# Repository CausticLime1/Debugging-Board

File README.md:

# sharkbyte

STM32H723 firmware for the SharkByte board.

## Prerequisites

- **Windows** (the build toolchain runs via PowerShell)
- **VSCode** with the [STM32 VSCode Extension](https://marketplace.visualstudio.com/items?itemName=stmicroelectronics.stm32-vscode-extension) installed
- **STM32CubeMX** 6.15.0+

## Getting started

### 1. Clone

```bash
git clone --recurse-submodules <repo-url>
```

### 2. Regenerate CubeMX files

Most of the ST-generated HAL and middleware files are not checked in — they're derived from `sharkbyte.ioc`. Regenerate them with:

**Command Palette → Run Task → STM32: CubeMX Codegen**

Or from the terminal:
```powershell
powershell -File .vscode/stm32cube.ps1 codegen
```

### 3. Build

**Command Palette → Run Task → STM32: Build Debug**

Or:
```powershell
powershell -File .vscode/stm32cube.ps1 build
```

### 4. Flash

Connect an ST-Link and run:

**Command Palette → Run Task → STM32: Flash And Run Debug**

This builds, flashes, and resets the board.

## Project structure

```
sharkbyte.ioc       # CubeMX project — source of truth for chip config
CMakeLists.txt      # Top-level build (manually maintained)
Core/Src/main.c     # Application entry point
Core/Src/encoder.cpp
Core/Inc/
gui/                # LVGL UI code
.vscode/
  stm32cube.ps1     # Build/flash/codegen script
  tasks.json        # VSCode task definitions
```

## Notes

- `Drivers/`, `Middlewares/` are gitignored — they are regenerated by CubeMX and should not be edited by hand
- The ST bundle versions (compiler, CMake, etc.) are pinned in `.settings/bundles-lock.store.json` and downloaded automatically by the ST extension on first open
- USB init function is disabled in CubeMX

### Linker script

The build uses `STM32H723XG_FLASH_custom.ld` (not the CubeMX-generated `STM32H723XG_FLASH.ld`). The custom file differs in three ways:

- `FLASH` region trimmed from 1024 KB to 896 KB (sectors 0–6)
- `NV_STORAGE` region added at sector 7 (`0x080E0000`, 128 KB) for persistent settings
- `.dma_buf` section placed at a fixed address in RAM_D1 (`0x24010000`, after the 64 KB LVGL heap) — LVGL draw buffers must live in the CPU's D1 domain to avoid the STM32H7 D1→D2 interconnect write-buffer coherency issue with DMA1

CubeMX regeneration overwrites `STM32H723XG_FLASH.ld` but does not touch the custom file. If the device config changes in a way that affects flash or RAM layout (e.g. stack/heap sizes), diff `STM32H723XG_FLASH.ld` against `STM32H723XG_FLASH_custom.ld` and merge any relevant changes manually.

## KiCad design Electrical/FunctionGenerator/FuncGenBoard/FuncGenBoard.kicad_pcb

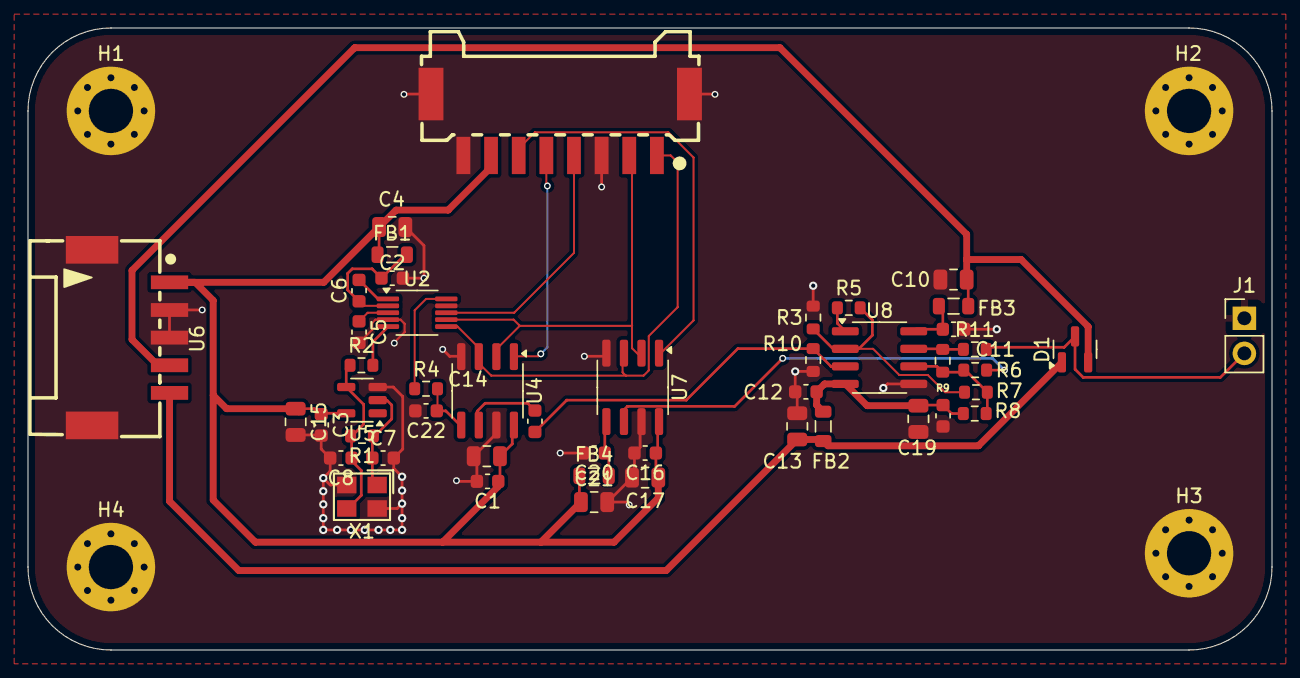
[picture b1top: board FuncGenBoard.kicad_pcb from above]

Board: 2 copper layers, 90.0 x 45.0 mm, 51 parts (0 on the bottom side), 28 nets.

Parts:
C1, C2, C3, C5, C11, C12, C16, C18, C20: 100nF; C_0603_1608Metric
C4, C9, C10, C13, C15, C17, C19, C21: 10uF; C_0805_2012Metric
C6: 10nF; C_0603_1608Metric
C7, C8: 18pF; C_0603_1608Metric
C14: 1uF; C_0603_1608Metric
C22: 100p; C_0603_1608Metric
D1: BAT54S; SOT-23
FB1, FB2, FB3, FB4: 600R@100MHz; L_0805_2012Metric
H1, H2, H3, H4: MountingHole_Pad; MountingHole_3.2mm_M3_Pad_Via
J1: Conn_01x02_Pin; PinHeader_1x02_P2.54mm_Vertical
R1: 1M; R_0603_1608Metric
R2: 33; R_0603_1608Metric
R3: 1k; R_0603_1608Metric
R4: 220; R_0603_1608Metric
R5: 4k; R_0603_1608Metric
R6, R7: 5.6k; R_0603_1608Metric
R8: 39K; R_0603_1608Metric
R9: 39k; R_0603_1608Metric
R10: 100k; R_0603_1608Metric
R11: 50; R_0603_1608Metric
U2: AD9833xRM; MSOP-10_3x3mm_P0.5mm
U4, U7: MCP4151-xxxx-P; SOIC-8_3.9x4.9mm_P1.27mm
U5: SN74LVC1GU04DBVR; SOT-23-5
U6: SM05B-PASS-TBT(LF)(SN); CONN-SMD_5P-P2.00_SM05B-PASS-TBT-LF-SN
U8: LM6172IMX/NOPB; SOIC-8_3.9x4.9mm_P1.27mm
U14: SM08B-PASS-TBT(LF)(SN); CONN-SMD_SM08B-PASS-TBT-LF-SN
X1: X322525MOB4SI; CRYSTAL-SMD_4P-L3.2-W2.5-BL

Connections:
+3.3V: C1.1, C3.1, C4.1, C9.1, C15.1, C16.1, C17.1, C21.1, FB1.1, FB4.1, U4.8 (V_{DD}), U5.5 (VCC), U6.1, U7.8 (V_{DD}), U14.7
+12V: C10.1, D1.2 (K), FB3.2, U6.4
-12V: C13.1, D1.1 (A), FB2.1, U6.5
/3.3_DIGI: C20.1, FB4.2, U7.5 (P0A)
/A_NINV: C14.1, R10.1, U8.3 (INA+)
/A_OUT: R3.1, R5.2, R7.1, U8.2 (INA-)
/B_OUT: R9.2, R11.1, U8.7 (OUTB)
/CS_AD9833: U2.8 (~FSYNC), U14.4
/CS_GAIN: U4.1 (~CS), U14.5
/CS_OFFSET: U7.1 (~CS), U14.6
/DIGI_OFST: R6.2, U7.6 (P0W)
/GEN_OUT: C22.1, R4.2, U4.5 (P0A)
/MCLK: R2.2, U2.5 (MCLK)
/SCLK: U2.7 (SCLK), U4.2 (SCK), U7.2 (SCK), U14.2
/SDATA: U2.6 (SDATA), U4.3 (SDI/SDO), U7.3 (SDI/SDO), U14.1
/V+: C11.1, FB3.1, U8.8 (V+)
/V-: C12.1, C18.1, C19.1, FB2.2, R8.1, U8.4 (V-)
GND: C1.2, C2.2, C3.2, C4.2, C5.2, C7.2, C8.2, C9.2, C10.2, C11.2, C12.2, C13.2, C15.2, C16.2, C17.2, C18.2, C19.2, C20.2, C21.2, C22.2, H1.1, H2.1, H3.1, H4.1, J1.1, R3.2, R10.2, U2.4 (DGND), U2.9 (AGND), U4.4 (V_{SS}), U4.7 (P0B), U5.3 (GND), U6.2, U6.3, U6.6, U6.7, U7.4 (V_{SS}), U7.7 (P0B), U8.5 (INB+), U14.3, U14.8, U14.9, U14.10, X1.2 (GND), X1.4 (GND)
unnamed: D1.3 (COM), J1.2, R11.2
unnamed: C5.1, U2.3 (CAP/2.5V)
unnamed: C6.2, U2.1 (COMP)
unnamed: C2.1, C6.1, FB1.2, U2.2 (VDD)
unnamed: R4.1, U2.10 (VOUT)
unnamed: C14.2, U4.6 (P0W)
unnamed: C7.1, R1.1, U5.2 (A), X1.1 (OSC1)
unnamed: C8.1, R1.2, R2.1, U5.4 (Y), X1.3 (OSC2)
unnamed: R6.1, R7.2, R8.2, R9.1, U8.6 (INB-)
unnamed: R5.1, U8.1 (OUTA)

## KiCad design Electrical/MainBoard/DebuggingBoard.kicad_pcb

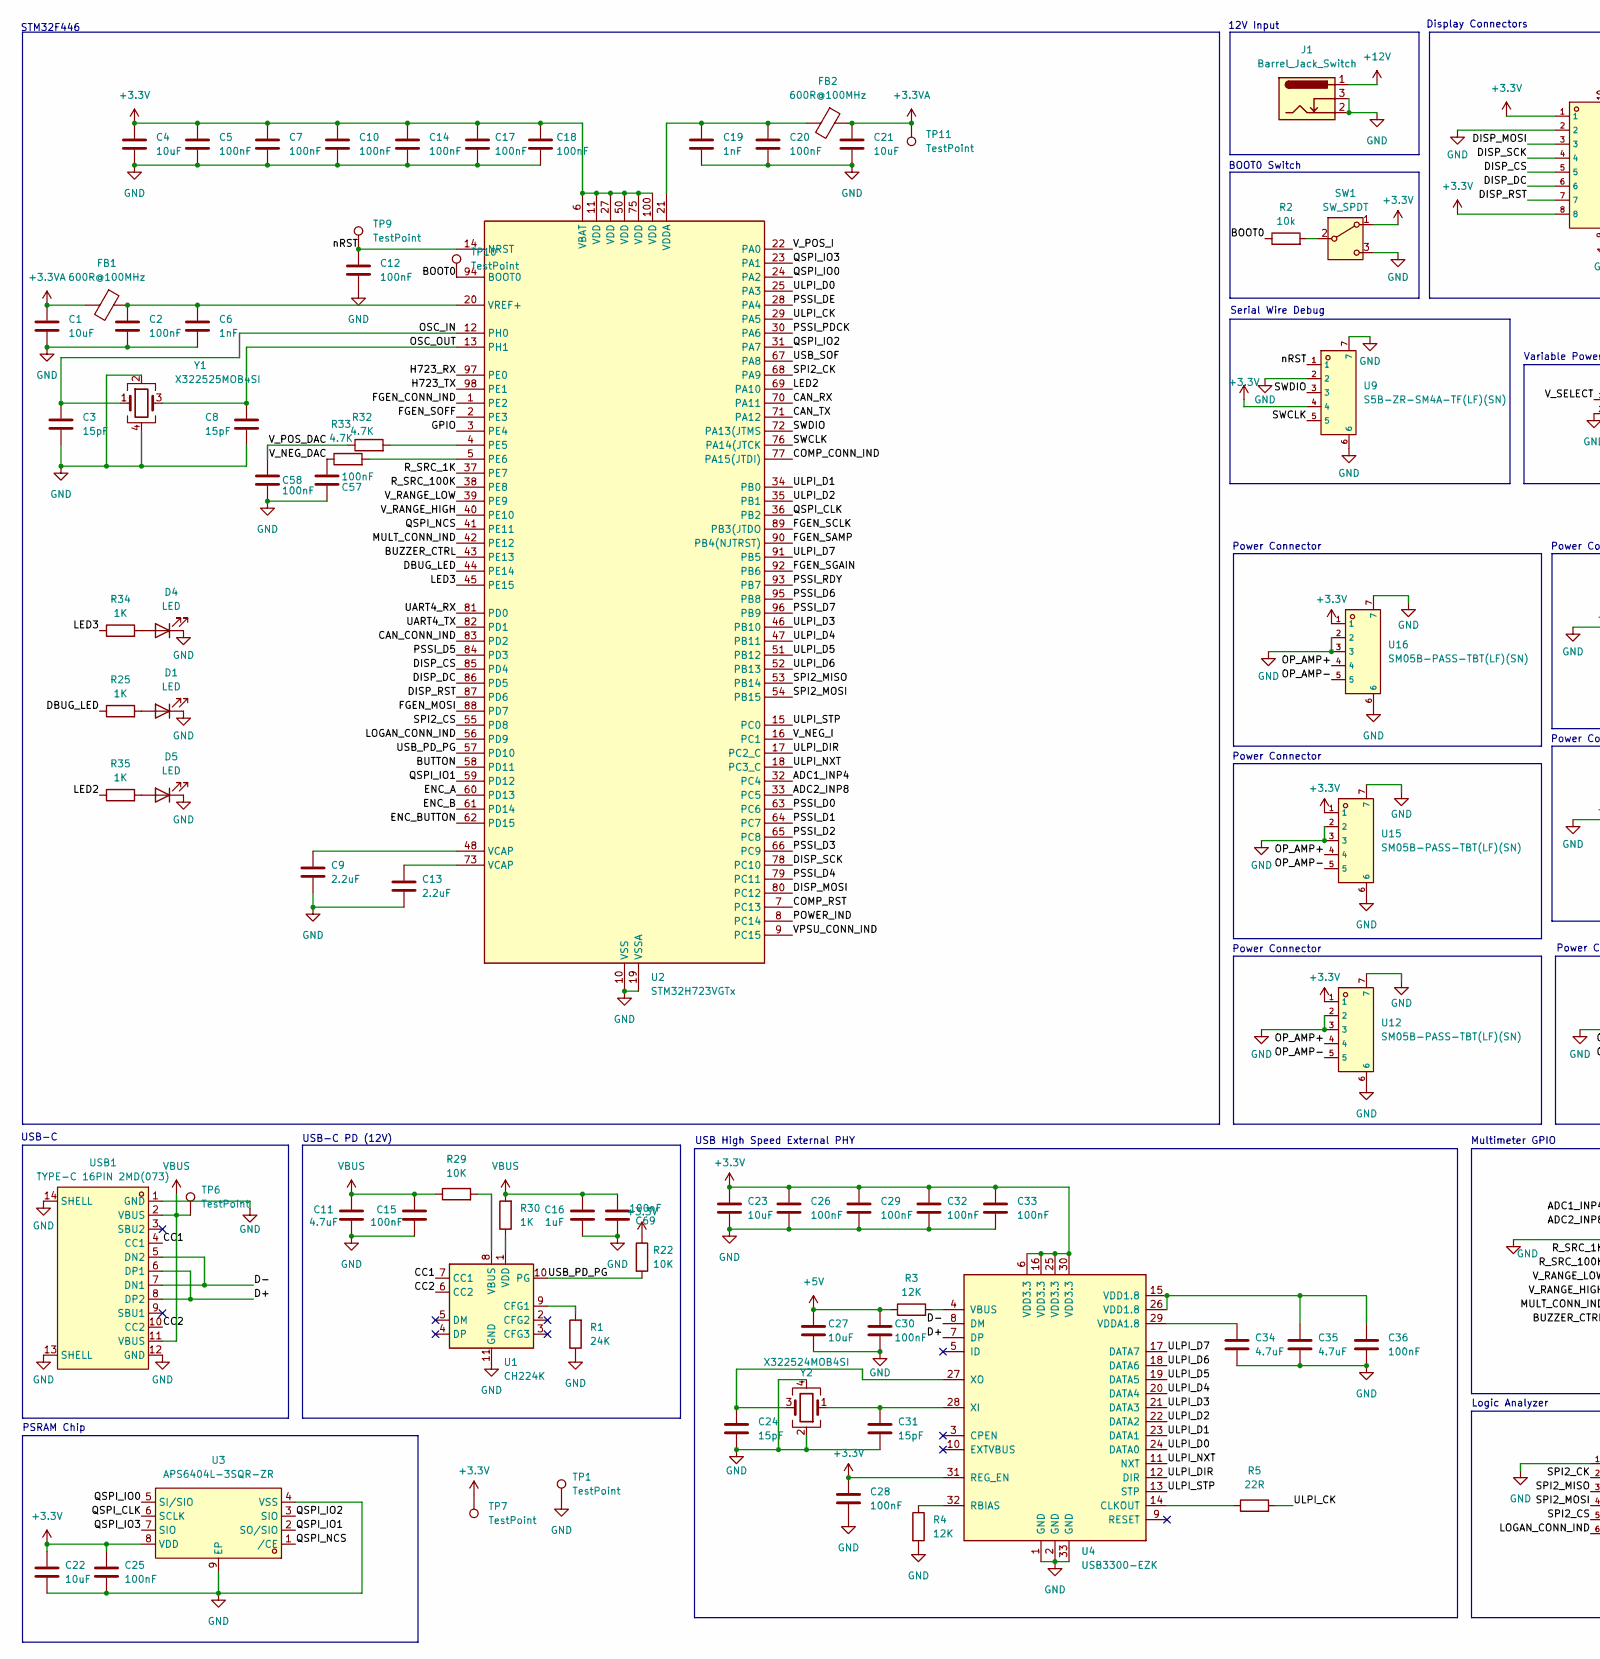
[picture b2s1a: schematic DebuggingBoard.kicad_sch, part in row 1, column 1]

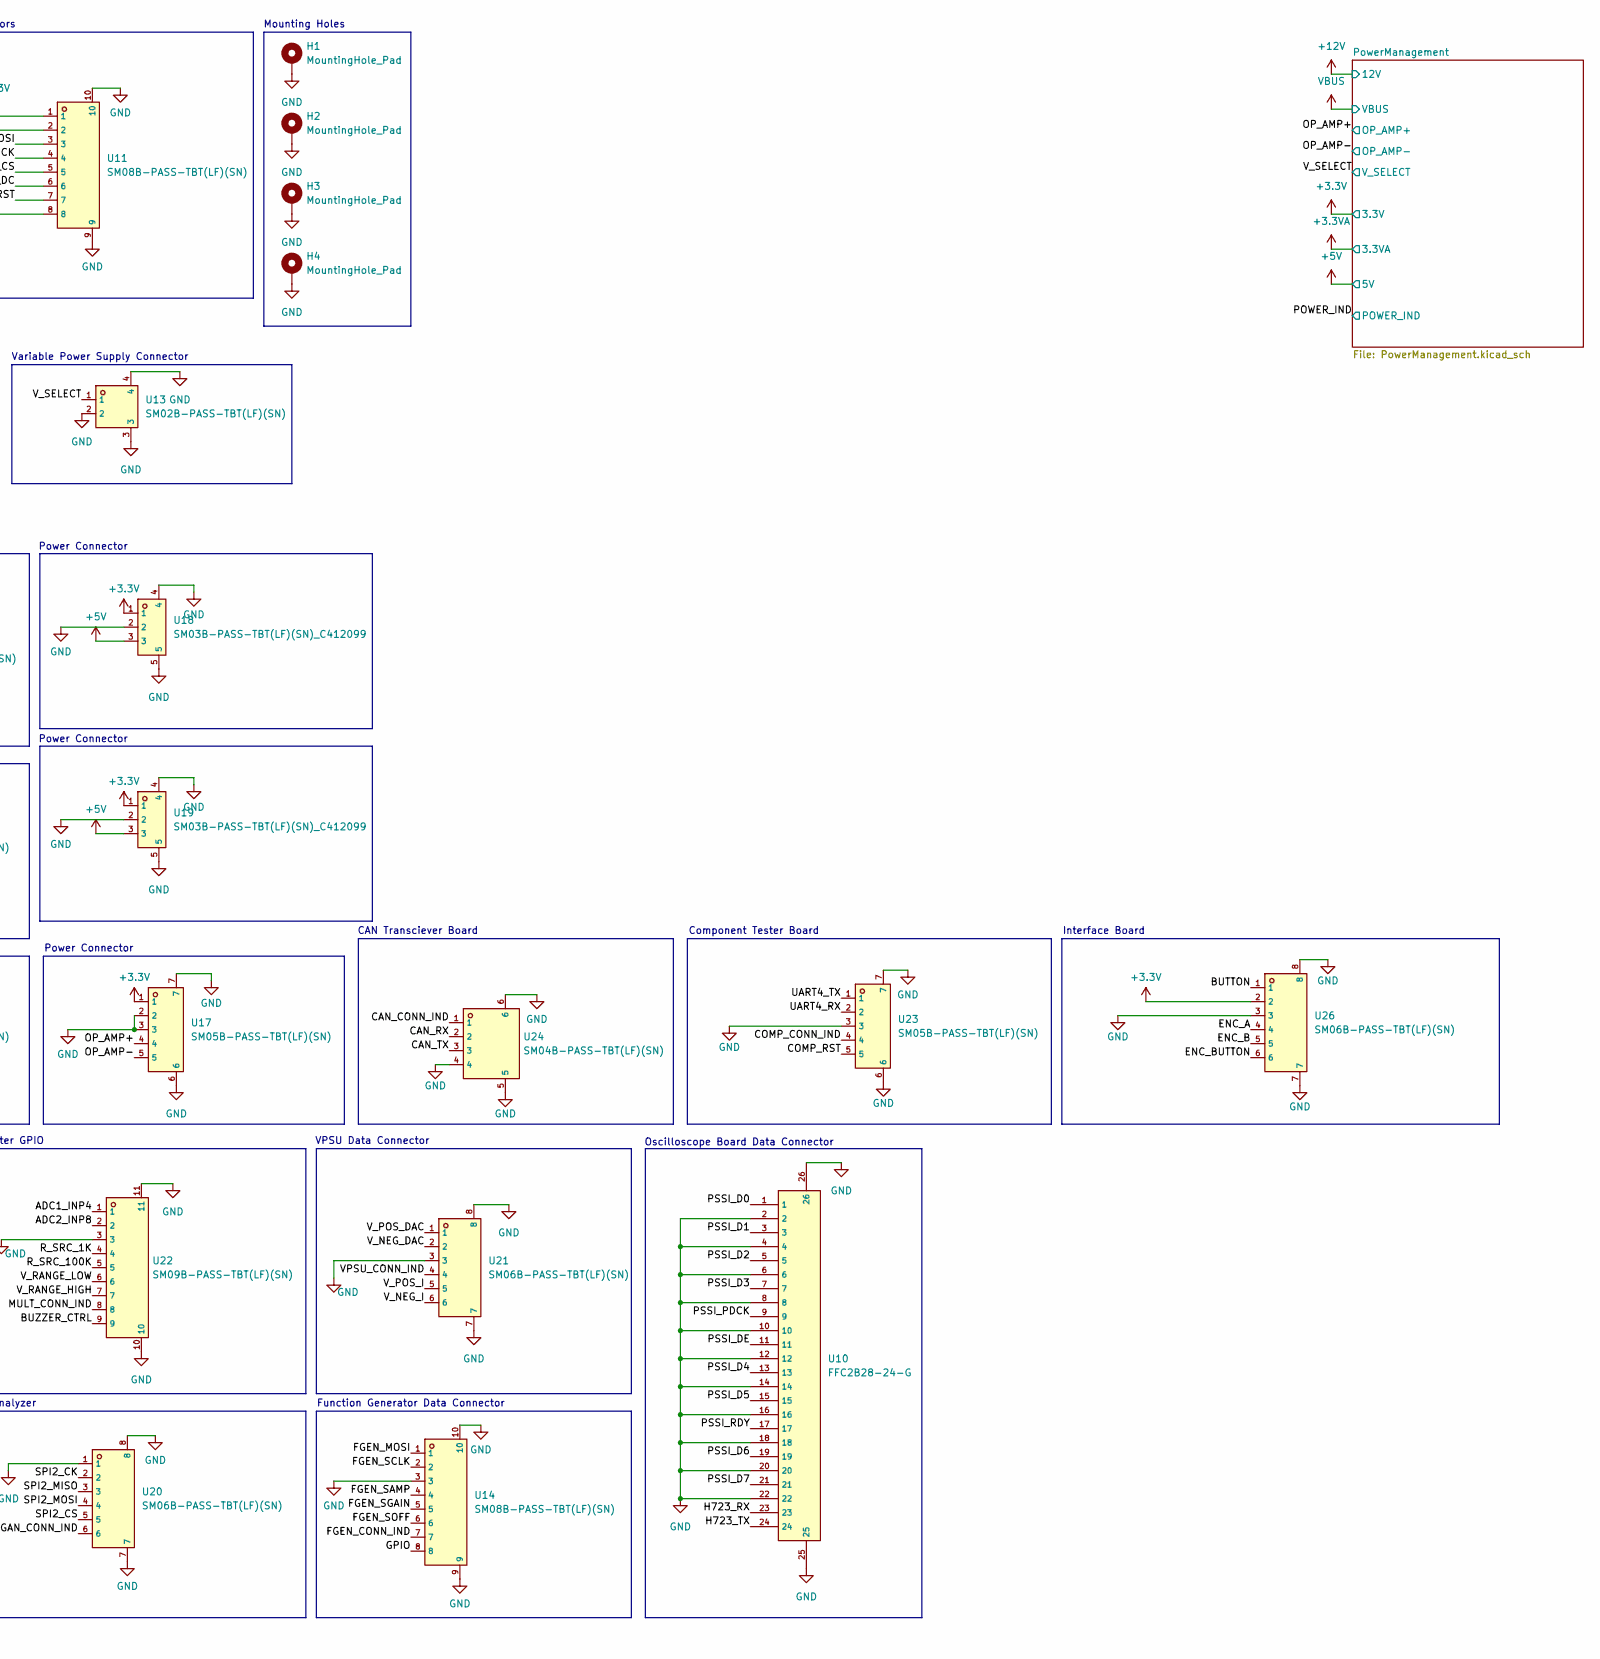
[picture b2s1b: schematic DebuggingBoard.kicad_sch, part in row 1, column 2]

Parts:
C1, C4, C21, C22, C23, C27: 10uF; C_0603_1608Metric
C2, C5, C7, C10, C12, C14, C15, C17, C18, C20, C25, C26, C28, C29, C30, C32, C33, C36, C57, C58, C69: 100nF; C_0402_1005Metric
C3, C8, C24, C31: 15pF; C_0402_1005Metric
C6, C19: 1nF; C_0402_1005Metric
C9, C13: 2.2uF; C_0603_1608Metric
C11: 4.7uF; C_0603_1608Metric
C16: 1uF; C_0603_1608Metric
C34, C35: 4.7uF; C_0402_1005Metric
D1, D4, D5: LED; LED_0603_1608Metric
FB1, FB2: 600R@100MHz; L_0805_2012Metric
H1, H2, H3, H4: MountingHole_Pad; MountingHole_3.2mm_M3_Pad_Via
J1: Barrel_Jack_Switch; BarrelJack_Kycon_KLDX-0202-xC_Horizontal
R1: 24K; R_0603_1608Metric
R2: 10k; R_0402_1005Metric
R3, R4: 12K; R_0402_1005Metric
R5: 22R; R_0402_1005Metric
R22, R29: 10K; R_0402_1005Metric
R25, R34, R35: 1K; R_0402_1005Metric
R30: 1K; R_0603_1608Metric
R32, R33: 4.7K; R_0402_1005Metric
SW1: SW_SPDT; SW_SPDT_CK_JS102011SAQN
TP1, TP6, TP7, TP9, TP10, TP11: TestPoint; TestPoint_Pad_D2.0mm
U1: CH224K; SSOP-10-1EP_3.9x4.9mm_P1mm_EP2.1x3.3mm
U2: STM32H723VGTx; LQFP-100_14x14mm_P0.5mm
U3: APS6404L-3SQR-ZR; USON-8_L3.0-W2.0-P0.50-BL-EP; LCSC Part C3040877
U4: USB3300-EZK; QFN-32-1EP_5x5mm_P0.5mm_EP3.45x3.45mm
U9: S5B-ZR-SM4A-TF(LF)(SN); CONN-SMD_5P-P1.50_S5B-ZR-SM4A-TF-LF-SN; LCSC C485355
U10: FFC2B28-24-G; FPC-SMD_24P-P0.50_XKB_X05A10L24G; LCSC C3151659
U11, U14: SM08B-PASS-TBT(LF)(SN); CONN-SMD_SM08B-PASS-TBT-LF-SN; LCSC C496230
U12, U15, U16, U17, U23: SM05B-PASS-TBT(LF)(SN); CONN-SMD_5P-P2.00_SM05B-PASS-TBT-LF-SN; LCSC C485350
U13: SM02B-PASS-TBT(LF)(SN); CONN-SMD_SM02B-PASS-TBT; LCSC C265417
U18, U19: SM03B-PASS-TBT(LF)(SN)_C412099; CONN-SMD_SM03B-PASS-TBT; LCSC C412099
U20, U21, U26: SM06B-PASS-TBT(LF)(SN); CONN-SMD_SM06B-PASS-TBT; LCSC C489711
U22: SM09B-PASS-TBT(LF)(SN); CONN-SMD_SM09B-PASS-TBT; LCSC C489712
U24: SM04B-PASS-TBT(LF)(SN); CONN-SMD_SM04B-PASS-TBT-LF-SN; LCSC C265073
USB1: TYPE-C 16PIN 2MD(073); USB-C-SMD_TYPE-C-6PIN-2MD-073; LCSC Part C2765186
Y1: X322525MOB4SI; Crystal_SMD_3225-4Pin_3.2x2.5mm
Y2: X322524MOB4SI; Crystal_SMD_3225-4Pin_3.2x2.5mm

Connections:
+3.3V: C4.1, C5.1, C7.1, C10.1, C14.1, C17.1, C18.1, C22.1, C23.1, C25.1, C26.1, C28.1, C29.1, C32.1, C33.1, R22.1, SW1.1 (A), TP7.1, U2.6 (VBAT), U2.11 (VDD), U2.27 (VDD), U2.50 (VDD), U2.75 (VDD), U2.100 (VDD), U3.8 (VDD), U4.6 (VDD3.3), U4.16 (VDD3.3), U4.25 (VDD3.3), U4.30 (VDD3.3), U4.31 (REG_EN), U9.4, U11.1, U11.8, U12.1, U15.1, U16.1, U17.1, U18.1, U19.1, U26.2; also elsewhere on the board
+3.3VA: C1.1, C21.1, FB1.2, FB2.1, TP11.1; also elsewhere on the board
+5V: C27.1, C30.1, R3.1, U18.3, U19.3; also elsewhere on the board
+12V: J1.1; also elsewhere on the board
/ADC1_INP4: U2.32 (PC4), U22.1
/ADC2_INP8: U2.33 (PC5), U22.2
/BOOT0: R2.1, TP10.1, U2.94 (BOOT0)
/BUTTON: U2.58 (PD11), U26.1
/BUZZER_CTRL: U2.43 (PE13), U22.9
/CAN_CONN_IND: U2.83 (PD2), U24.1
/CAN_RX: U2.70 (PA11), U24.2
/CAN_TX: U2.71 (PA12), U24.3
/CC1: U1.7 (CC1), USB1.4 (CC1)
/CC2: U1.6 (CC2), USB1.10 (CC2)
/COMP_CONN_IND: U2.77 (PA15(JTDI)), U23.4
/COMP_RST: U2.7 (PC13), U23.5
/D+: U4.7 (DP), USB1.6 (DP1), USB1.8 (DP2)
/D-: U4.8 (DM), USB1.5 (DN2), USB1.7 (DN1)
/DBUG_LED: R25.1, U2.44 (PE14)
/DISP_CS: U2.85 (PD4), U11.5
/DISP_DC: U2.86 (PD5), U11.6
/DISP_MOSI: U2.80 (PC12), U11.3
/DISP_RST: U2.87 (PD6), U11.7
/DISP_SCK: U2.78 (PC10), U11.4
/ENC_A: U2.60 (PD13), U26.4
/ENC_B: U2.61 (PD14), U26.5
/ENC_BUTTON: U2.62 (PD15), U26.6
/FGEN_CONN_IND: U2.1 (PE2), U14.7
/FGEN_MOSI: U2.88 (PD7), U14.1
/FGEN_SAMP: U2.90 (PB4(NJTRST)), U14.4
/FGEN_SCLK: U2.89 (PB3(JTDO), U14.2
/FGEN_SGAIN: U2.92 (PB6), U14.5
/FGEN_SOFF: U2.2 (PE3), U14.6
/GPIO: U2.3 (PE4), U14.8
/H723_RX: U2.97 (PE0), U10.23
/H723_TX: U2.98 (PE1), U10.24
/LED2: R35.1, U2.69 (PA10)
/LED3: R34.1, U2.45 (PE15)
/LOGAN_CONN_IND: U2.56 (PD9), U20.6
/MULT_CONN_IND: U2.42 (PE12), U22.8
/OP_AMP+: U12.4, U15.4, U16.4, U17.4; also elsewhere on the board
/OP_AMP-: U12.5, U15.5, U16.5, U17.5; also elsewhere on the board
/OSC_IN: C3.1, U2.12 (PH0), Y1.1
/OSC_OUT: C8.1, U2.13 (PH1), Y1.3
/POWER_IND: U2.8 (PC14); also elsewhere on the board
/PSSI_D0: U2.63 (PC6), U10.1
/PSSI_D1: U2.64 (PC7), U10.3
/PSSI_D2: U2.65 (PC8), U10.5
/PSSI_D3: U2.66 (PC9), U10.7
/PSSI_D4: U2.79 (PC11), U10.13
/PSSI_D5: U2.84 (PD3), U10.15
/PSSI_D6: U2.95 (PB8), U10.19
/PSSI_D7: U2.96 (PB9), U10.21
/PSSI_DE: U2.28 (PA4), U10.11
/PSSI_PDCK: U2.30 (PA6), U10.9
/PSSI_RDY: U2.93 (PB7), U10.17
/QSPI_CLK: U2.36 (PB2), U3.6 (SCLK)
/QSPI_IO0: U2.24 (PA2), U3.5 (SI/SIO)
/QSPI_IO1: U2.59 (PD12), U3.2 (SO/SIO)
/QSPI_IO2: U2.31 (PA7), U3.3 (SIO)
/QSPI_IO3: U2.23 (PA1), U3.7 (SIO)
/QSPI_NCS: U2.41 (PE11), U3.1 (/CE)
/R_SRC_1K: U2.37 (PE7), U22.4
/R_SRC_100K: U2.38 (PE8), U22.5
/SPI2_CK: U2.68 (PA9), U20.2
/SPI2_CS: U2.55 (PD8), U20.5
/SPI2_MISO: U2.53 (PB14), U20.3
/SPI2_MOSI: U2.54 (PB15), U20.4
/SWCLK: U2.76 (PA14(JTCK), U9.5
/SWDIO: U2.72 (PA13(JTMS), U9.3
/UART4_RX: U2.81 (PD0), U23.2
/UART4_TX: U2.82 (PD1), U23.1
/ULPI_CK: R5.2, U2.29 (PA5)
/ULPI_D0: U2.25 (PA3), U4.24 (DATA0)
/ULPI_D1: U2.34 (PB0), U4.23 (DATA1)
/ULPI_D2: U2.35 (PB1), U4.22 (DATA2)
/ULPI_D3: U2.46 (PB10), U4.21 (DATA3)
/ULPI_D4: U2.47 (PB11), U4.20 (DATA4)
/ULPI_D5: U2.51 (PB12), U4.19 (DATA5)
/ULPI_D6: U2.52 (PB13), U4.18 (DATA6)
/ULPI_D7: U2.91 (PB5), U4.17 (DATA7)
/ULPI_DIR: U2.17 (PC2_C), U4.12 (DIR)
/ULPI_NXT: U2.18 (PC3_C), U4.11 (NXT)
/ULPI_STP: U2.15 (PC0), U4.13 (STP)
/USB_PD_PG: R22.2, U1.10 (PG), U2.57 (PD10)
/USB_SOF: U2.67 (PA8)
/VPSU_CONN_IND: U2.9 (PC15), U21.4
/V_NEG_DAC: C57.1, R33.1, U21.2
/V_NEG_I: U2.16 (PC1), U21.6
/V_POS_DAC: C58.1, R32.1, U21.1
/V_POS_I: U2.22 (PA0), U21.5
/V_RANGE_HIGH: U2.40 (PE10), U22.7
/V_RANGE_LOW: U2.39 (PE9), U22.6
/V_SELECT: U13.1; also elsewhere on the board
/nRST: C12.1, TP9.1, U2.14 (NRST), U9.1
GND: C1.2, C2.2, C3.2, C4.2, C5.2, C6.2, C7.2, C8.2, C9.2, C10.2, C11.1, C12.2, C13.2, C14.2, C15.1, C16.1, C17.2, C18.2, C19.2, C20.2, C21.2, C22.2, C23.2, C24.2, C25.2, C26.2, C27.2, C28.2, C29.2, C30.2, C31.2, C32.2, C33.2, C34.2, C35.2, C36.2, C57.2, C58.2, C69.2, D1.1 (K), D4.1 (K), D5.1 (K), H1.1, H2.1, H3.1, H4.1, J1.2, J1.3, R1.1, R4.2, SW1.3 (C), TP1.1, U1.11 (GND), U2.10 (VSS), U2.19 (VSSA), U2.26 (VSS), U2.49 (VSS), U2.74 (VSS), U2.99 (VSS), U3.4 (VSS), U3.9 (EP), U4.1 (GND), U4.2 (GND), U4.33 (GND), U9.2, U9.6, U9.7, U10.2, U10.4, U10.6, U10.8, U10.10, U10.12, U10.14, U10.16, U10.18, U10.20, U10.22, U10.25, U10.26, U11.2, U11.9, U11.10, U12.2, U12.3, U12.6, U12.7, U13.2, U13.3, U13.4, U14.3, U14.9, U14.10, U15.2, U15.3, U15.6, U15.7, U16.2, U16.3, U16.6, U16.7, U17.2, U17.3, U17.6, U17.7, U18.2, U18.4, U18.5, U19.2, U19.4, U19.5, U20.1, U20.7, U20.8, U21.3, U21.7, U21.8, U22.3, U22.10, U22.11, U23.3, U23.6, U23.7, U24.4, U24.5, U24.6, U26.3, U26.7, U26.8, USB1.1 (GND), USB1.12 (GND), USB1.13 (SHELL), USB1.14 (SHELL), Y1.2, Y1.4, Y2.2, Y2.4; also elsewhere on the board
unnamed: C9.1, U2.48 (VCAP)
unnamed: C13.1, U2.73 (VCAP)
unnamed: C35.1, C36.1, U4.15 (VDD1.8), U4.26 (VDD1.8)
unnamed: D1.2 (A), R25.2
unnamed: D4.2 (A), R34.2
unnamed: D5.2 (A), R35.2
unnamed: R2.2, SW1.2 (B)
unnamed: R1.2, U1.9 (CFG1)
unnamed: R29.2, U1.8 (VBUS)
unnamed: R30.1, U1.1 (VDD)
unnamed: R32.2, U2.4 (PE5)
unnamed: R33.2, U2.5 (PE6)
unnamed: C19.1, C20.1, FB2.2, U2.21 (VDDA)
unnamed: C2.1, C6.1, FB1.1, U2.20 (VREF+)
unnamed: R5.1, U4.14 (CLKOUT)
unnamed: R4.1, U4.32 (RBIAS)
unnamed: R3.2, U4.4 (VBUS)
unnamed: C34.1, U4.29 (VDDA1.8)
unnamed: C31.1, U4.28 (XI), Y2.1
unnamed: C24.1, U4.27 (XO), Y2.3
VBUS: C11.2, C15.2, C16.2, C69.1, R29.1, R30.2, TP6.1, USB1.2 (VBUS), USB1.11 (VBUS); also elsewhere on the board

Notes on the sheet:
USB-C
Oscilloscope Board Data Connector
Mounting Holes
PSRAM Chip
Power Connector
Interface Board
Component Tester Board
BOOT0 Switch
CAN Transciever Board
USB High Speed External PHY
USB-C PD (12V)
Variable Power Supply Connector
Function Generator Data Connector
Display Connectors
Logic Analyzer
Multimeter GPIO
12V Input
STM32F446
Serial Wire Debug
VPSU Data Connector

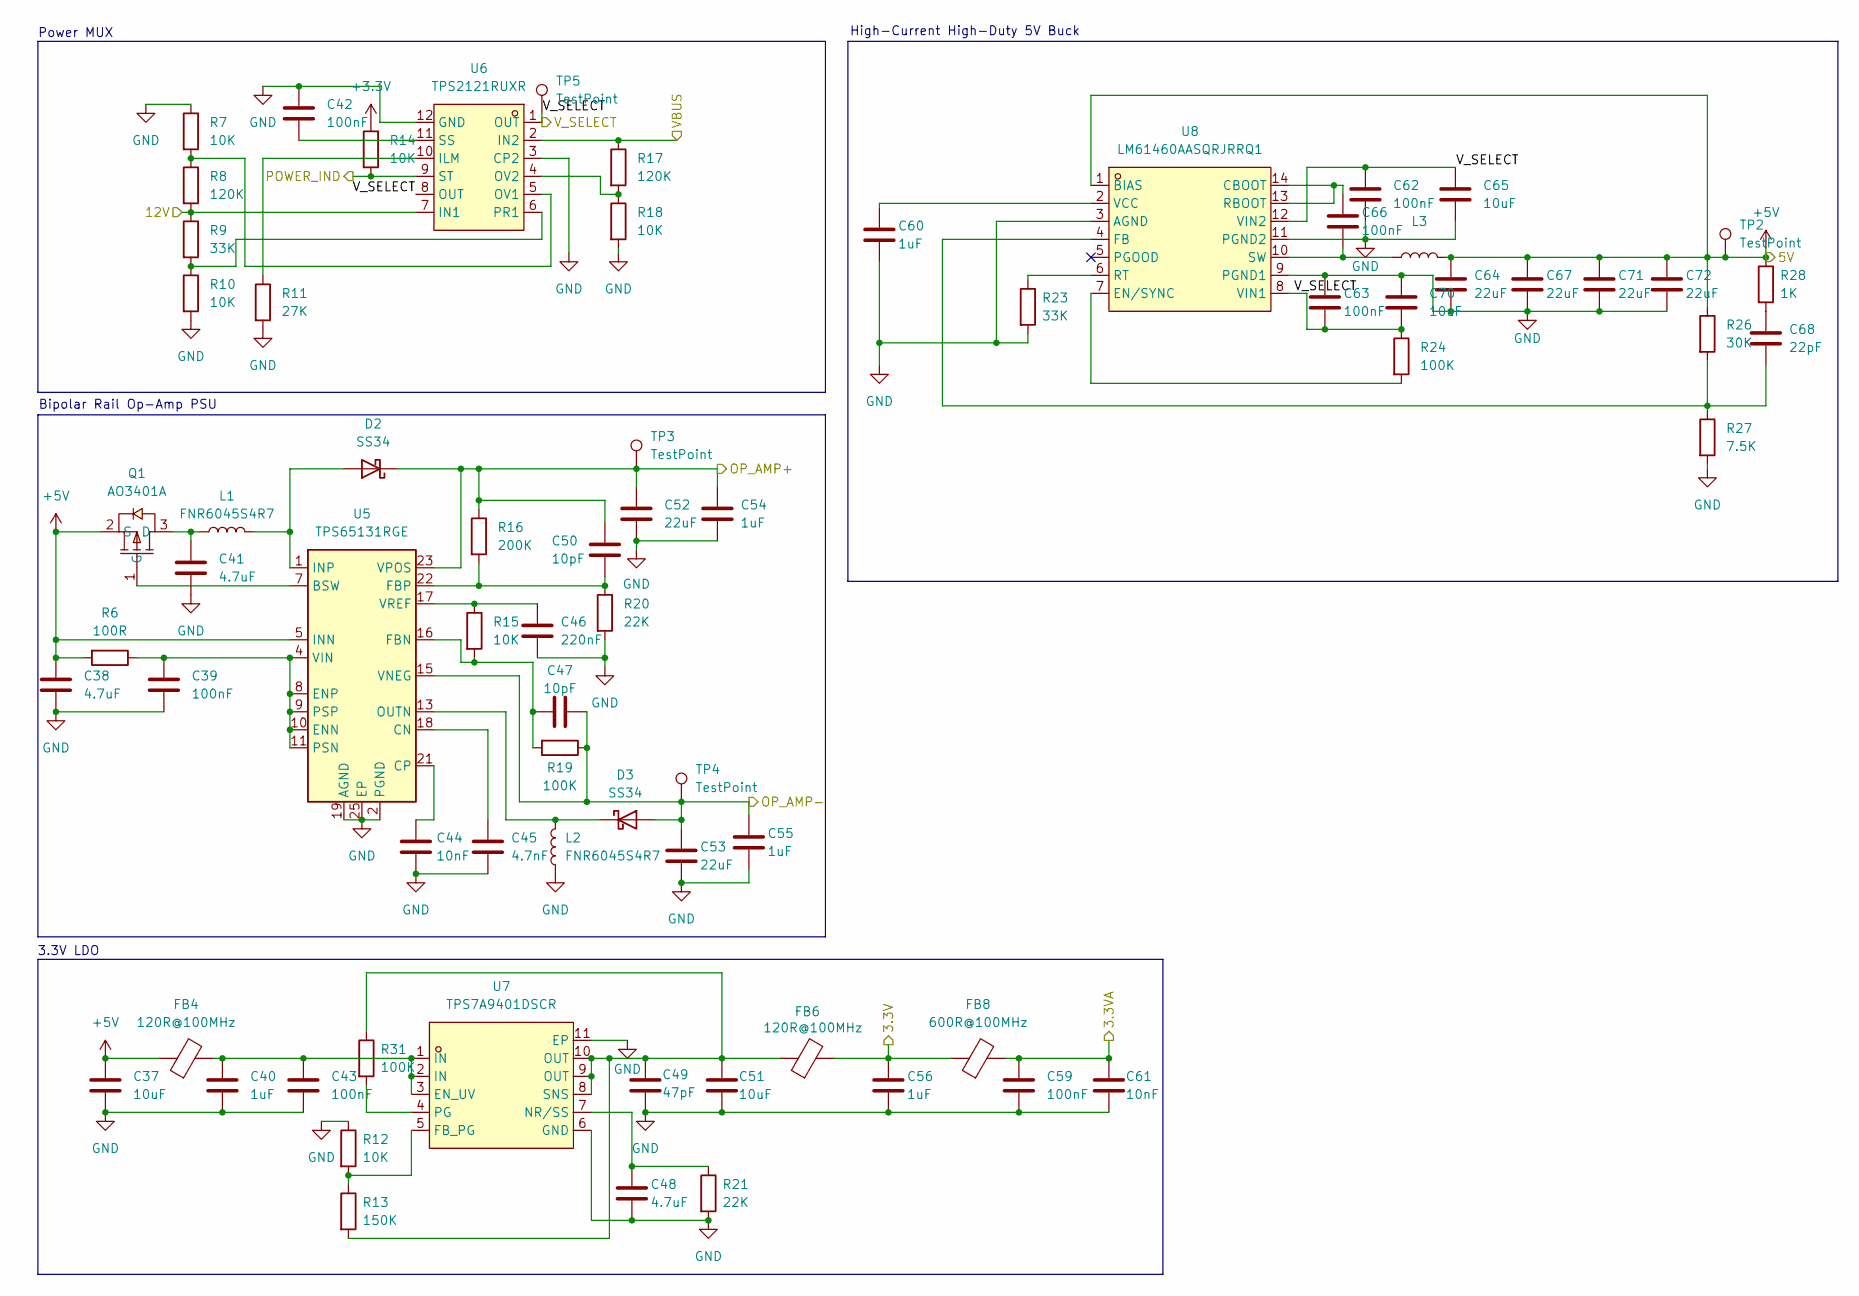
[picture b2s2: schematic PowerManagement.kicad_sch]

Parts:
C37, C51, C65, C70: 10uF; C_0603_1608Metric
C38, C41, C48: 4.7uF; C_0603_1608Metric
C39, C42, C43, C59, C62, C63, C66: 100nF; C_0402_1005Metric
C40, C54, C55, C56, C60: 1uF; C_0603_1608Metric
C44, C61: 10nF; C_0402_1005Metric
C45: 4.7nF; C_0402_1005Metric
C46: 220nF; C_0402_1005Metric
C47, C50: 10pF; C_0402_1005Metric
C49: 47pF; C_0402_1005Metric
C52, C53, C64, C67, C71, C72: 22uF; C_0805_2012Metric
C68: 22pF; C_0402_1005Metric
D2, D3: SS34; D_SMA
FB4, FB6: 120R@100MHz; L_0603_1608Metric
FB8: 600R@100MHz; L_0805_2012Metric
L1, L2, L3: FNR6045S4R7; L_Changjiang_FNR6045S
Q1: AO3401A; SOT-23_L2.9-W1.3-P1.90-LS2.4-BR; LCSC Part C15127
R6: 100R; R_0402_1005Metric
R7, R10, R18: 10K; R_0603_1608Metric
R8, R17: 120K; R_0603_1608Metric
R9: 33K; R_0603_1608Metric
R11: 27K; R_0603_1608Metric
R12, R14, R15: 10K; R_0402_1005Metric
R13: 150K; R_0603_1608Metric
R16: 200K; R_0402_1005Metric
R19, R24, R31: 100K; R_0402_1005Metric
R20, R21: 22K; R_0402_1005Metric
R23: 33K; R_0402_1005Metric
R26: 30K; R_0603_1608Metric
R27: 7.5K; R_0603_1608Metric
R28: 1K; R_0402_1005Metric
TP2, TP3, TP4, TP5: TestPoint; TestPoint_Pad_D2.0mm
U5: TPS65131RGE; VQFN-24-1EP_4x4mm_P0.5mm_EP2.45x2.45mm_ThermalVias
U6: TPS2121RUXR; VQFN-HR-12_L2.5-W2.0-P0.50-BL; LCSC Part C485916
U7: TPS7A9401DSCR; WSON-10_L3.0-W3.0-P0.50-TL-EP; LCSC Part C5220127
U8: LM61460AASQRJRRQ1; VQFN-14-HR_L4.0-W3.5-TL_LM61460AASQRJRRQ1; LCSC Part C1855832

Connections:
+3.3V: C56.1, FB6.2, FB8.1, R14.1; also elsewhere on the board
+3.3VA: C59.1, C61.1, FB8.2; also elsewhere on the board
+5V: C37.1, C38.1, C64.1, C67.1, C71.1, C72.1, FB4.1, L3.2, Q1.2 (S), R6.2, R26.1, R28.1, TP2.1, U5.5 (INN), U5.6 (INN), U8.1 (BIAS); also elsewhere on the board
+12V: R8.2, R9.1, U6.7 (IN1); also elsewhere on the board
/OP_AMP+: C50.1, C52.1, C54.1, D2.1 (K), R16.1, TP3.1, U5.23 (VPOS); also elsewhere on the board
/OP_AMP-: C47.2, C53.1, C55.1, D3.2 (A), R19.1, TP4.1, U5.15 (VNEG); also elsewhere on the board
/POWER_IND: R14.2, U6.9 (ST); also elsewhere on the board
/V_SELECT: C62.1, C63.2, C65.1, C70.2, R24.1, TP5.1, U6.1 (OUT), U6.8 (OUT), U8.8 (VIN1), U8.12 (VIN2); also elsewhere on the board
GND: C37.2, C38.2, C39.2, C40.2, C41.2, C42.1, C43.2, C44.2, C45.2, C46.2, C48.2, C49.2, C51.2, C52.2, C53.2, C54.2, C55.2, C56.2, C59.2, C60.2, C61.2, C62.2, C63.1, C64.2, C65.2, C67.2, C70.1, C71.2, C72.2, L2.1, R7.1, R10.2, R11.2, R12.1, R18.2, R20.2, R21.2, R23.2, R27.2, U5.2 (PGND), U5.3 (PGND), U5.19 (AGND), U5.25 (EP), U6.3 (CP2), U6.12 (GND), U7.6 (GND), U7.11 (EP), U8.3 (AGND), U8.9 (PGND1), U8.11 (PGND2); also elsewhere on the board
unnamed: C68.1, R28.2
unnamed: D2.2 (A), L1.2, U5.1 (INP), U5.24 (INP)
unnamed: D3.1 (K), L2.2, U5.13 (OUTN), U5.14 (OUTN)
unnamed: C41.1, L1.1, Q1.3 (D)
unnamed: Q1.1 (G), U5.7 (BSW)
unnamed: C45.1, U5.18 (CN)
unnamed: C44.1, U5.21 (CP)
unnamed: C39.1, R6.1, U5.4 (VIN), U5.8 (ENP), U5.9 (PSP), U5.10 (ENN), U5.11 (PSN)
unnamed: C47.1, R15.2, R19.2, U5.16 (FBN)
unnamed: C50.2, R16.2, R20.1, U5.22 (FBP)
unnamed: C46.1, R15.1, U5.17 (VREF)
unnamed: R11.1, U6.10 (ILM)
unnamed: R7.2, R8.1, U6.5 (OV1)
unnamed: R17.2, R18.1, U6.4 (OV2)
unnamed: R9.2, R10.1, U6.6 (PR1)
unnamed: C42.2, U6.11 (SS)
unnamed: C40.1, C43.1, FB4.2, U7.1 (IN), U7.2 (IN), U7.3 (EN_UV)
unnamed: R12.2, R13.1, U7.5 (FB_PG)
unnamed: C48.1, R21.1, U7.7 (NR/SS)
unnamed: R31.2, U7.4 (PG)
unnamed: C49.1, C51.1, FB6.1, R13.2, R31.1, U7.8 (SNS), U7.9 (OUT), U7.10 (OUT)
unnamed: C66.1, U8.13 (RBOOT), U8.14 (CBOOT)
unnamed: R24.2, U8.7 (EN/SYNC)
unnamed: C68.2, R26.2, R27.1, U8.4 (FB)
unnamed: R23.1, U8.6 (RT)
unnamed: C66.2, L3.1, U8.10 (SW)
unnamed: C60.1, U8.2 (VCC)
VBUS: R17.1, U6.2 (IN2); also elsewhere on the board

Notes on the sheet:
Power MUX
High-Current High-Duty 5V Buck
Bipolar Rail Op-Amp PSU
3.3V LDO

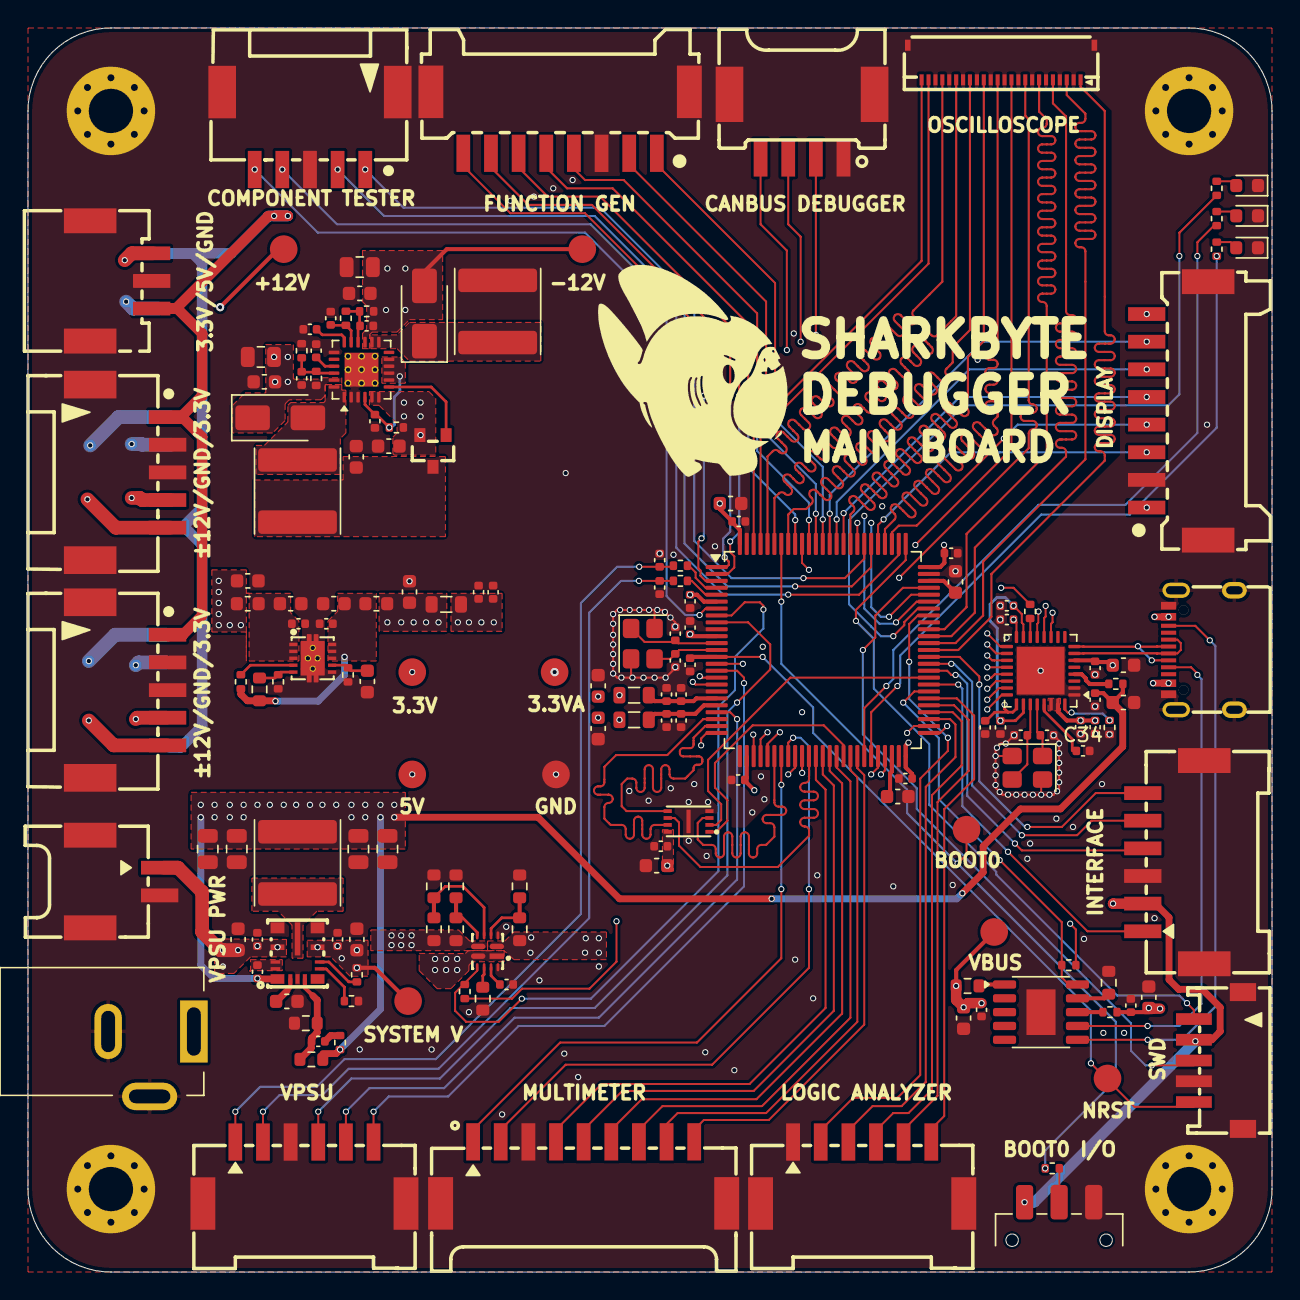
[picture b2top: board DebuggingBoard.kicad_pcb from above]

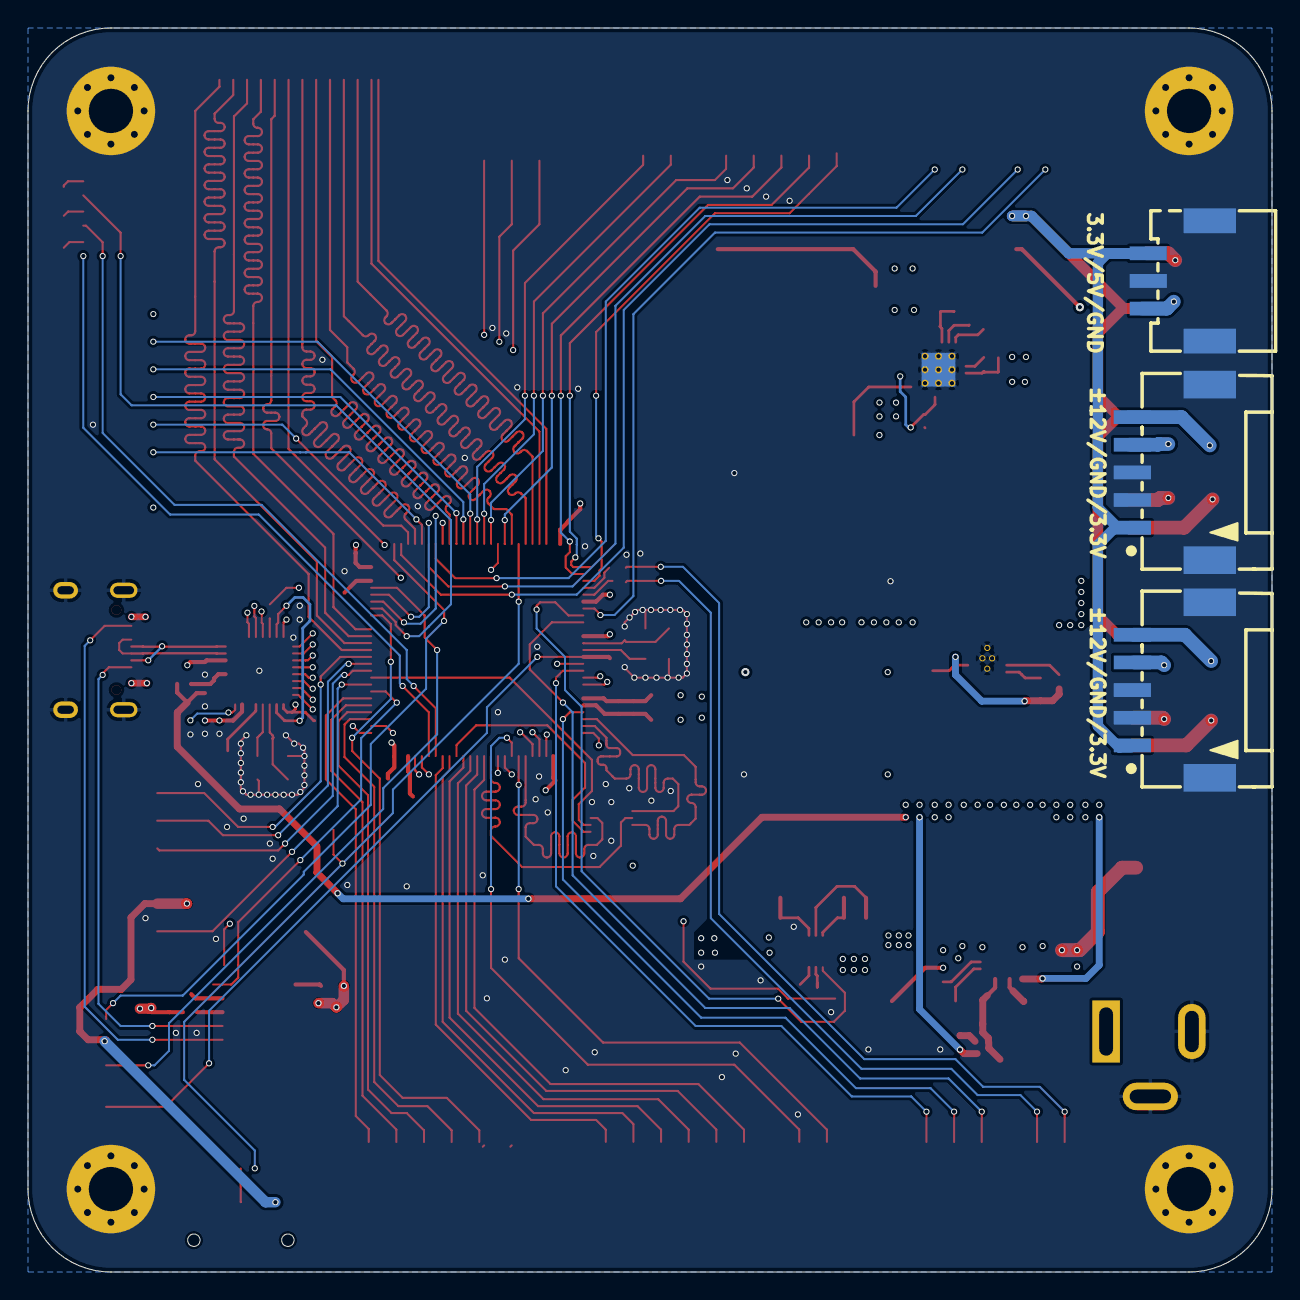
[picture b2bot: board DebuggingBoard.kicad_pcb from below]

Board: 6 copper layers, 90.0 x 90.0 mm, 165 parts (3 on the bottom side), 143 nets.

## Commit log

2025-10-11 init commit
2025-10-11 added proj file
2025-10-13 added sim files and osc
2025-10-21 nearly final osc
2025-12-27 rack approach
2025-12-30 updated main:
2026-01-03 VPSU and PMS complete
2026-01-05 modified power flow
2026-01-05 update all files names
2026-01-05 moved mainboard cubemx
2026-01-06 VPSU schem complete
2026-01-07 usb hs config
2026-01-08 function generator rough copy
2026-01-08 layout
2026-01-09 layout main
2026-01-12 2026-01-11
2026-01-13 new layout
2026-01-13 updated connectors
2026-01-13 vpsu conn
2026-01-15 finished main
2026-01-16 manufactured
2026-01-27 rm redundant main folder'
2026-01-29 software unit testing
2026-01-29 renamed folder to software
2026-02-01 debugging
2026-02-04 LCD Test
2026-02-09 more usb debug
2026-02-09 updated code
2026-02-10 freertos
2026-02-13 yolo
2026-03-07 init
2026-03-07 clean up
2026-03-10 Add ST7789-STM32 submodule
2026-03-11 st7789 baseline
2026-03-12 windows vscode setup
2026-03-12 st7789 working checkpoint
2026-03-13 cpp23
2026-03-14 lvgl init
2026-03-14 lvgl working demo
2026-03-15 reorganize
2026-03-15 LV_COLOR_FORMAT_RGB565_SWAPPED fix and theme demo
2026-03-15 persistant theme
2026-03-16 isolate gui
2026-03-18 gitignore, tasks, custom .ld
    - gitignore Drivers and Middlewares, use sharkbyte.ioc to generate
    - add stm32cube.ps1: actions driven by the ST bundle manager; finds cubemx via updater.ini (same lookup as the ST vscode extension)
    - add vscode tasks wired to stm32cube.ps1
    - relink to STM32H723XG_FLASH_custom.ld
    - readme
2026-03-19 syscfg switches
